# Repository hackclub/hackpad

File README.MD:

Talk to @Ace (Zohair shaik) on slack Gmail: Zohairshaik7@gmail.com Discord: autohackingcodes2079Hi this is my hackpad submission:

________________________________________________
Why I made it:

Was pretty bored and saw some macropads on insta so i got inspired..
________________________________________________
What I need:

7x Cherry MX switches
2x SK6812 MINI Leds
7x Blank DSA Keycaps
________________________________________________

______________________________________________
Firmware used:

KMK

_______________________________________________

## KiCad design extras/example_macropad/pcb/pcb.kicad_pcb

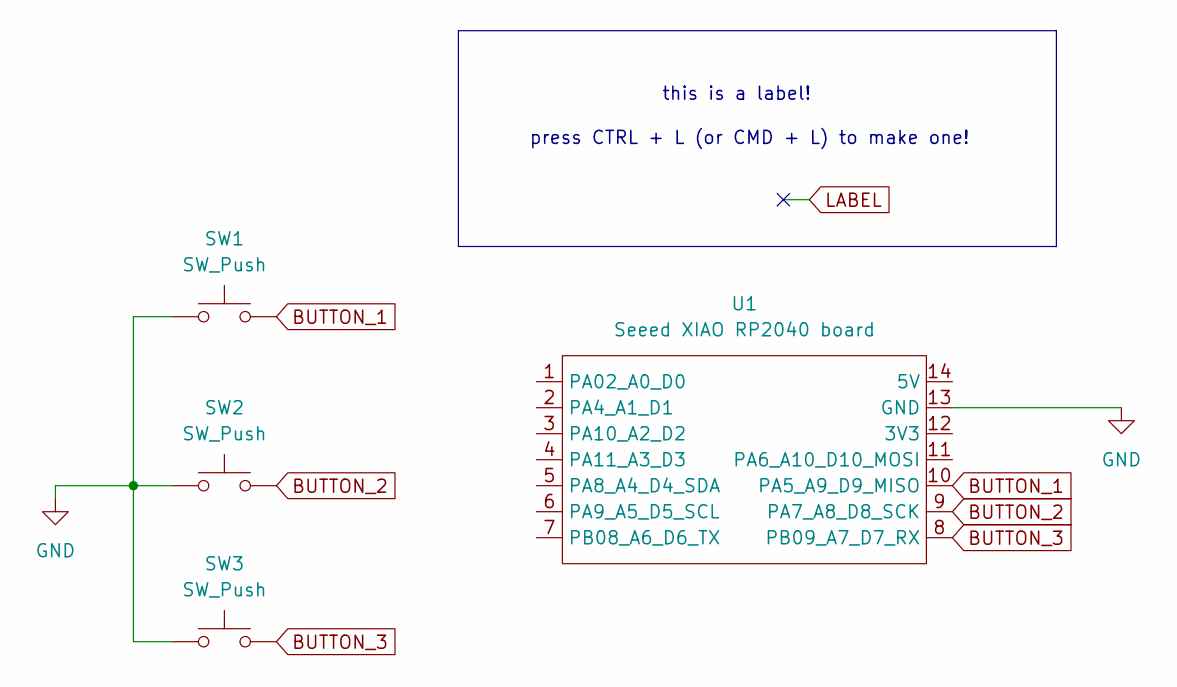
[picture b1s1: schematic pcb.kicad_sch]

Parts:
SW1, SW2, SW3: SW_Push; SW_Cherry_MX_1.00u_PCB
U1: Seeed XIAO RP2040 board; XIAO-Generic-Hybrid-14P-2.54-21X17.8MM

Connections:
BUTTON_1: SW1.2, U1.10 (PA5_A9_D9_MISO)
BUTTON_2: SW2.2, U1.9 (PA7_A8_D8_SCK)
BUTTON_3: SW3.2, U1.8 (PB09_A7_D7_RX)
GND: SW1.1, SW2.1, SW3.1, U1.13 (GND)

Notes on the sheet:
press CTRL + L (or CMD + L) to make one!
this is a label!

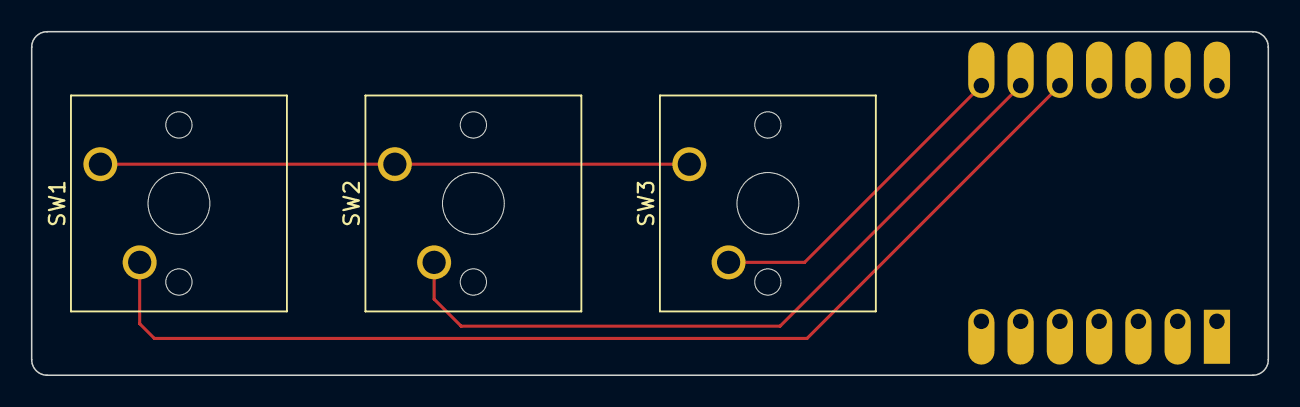
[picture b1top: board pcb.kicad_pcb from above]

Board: 2 copper layers, 80.0 x 22.2 mm, 4 parts (1 on the bottom side), 4 nets.

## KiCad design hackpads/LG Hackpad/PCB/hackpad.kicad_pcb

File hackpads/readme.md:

# madpad

* Keyboard Maintainer: [Meghana Madiraju](https://github.com/MeghanaM4)
* Hardware Supported: *The PCBs, controllers supported*
* Hardware Availability: *Links to where you can find this hardware*

Make example for this keyboard (after setting up your build environment):

    make madpad:default

Flashing example for this keyboard:

    make madpad:default:flash

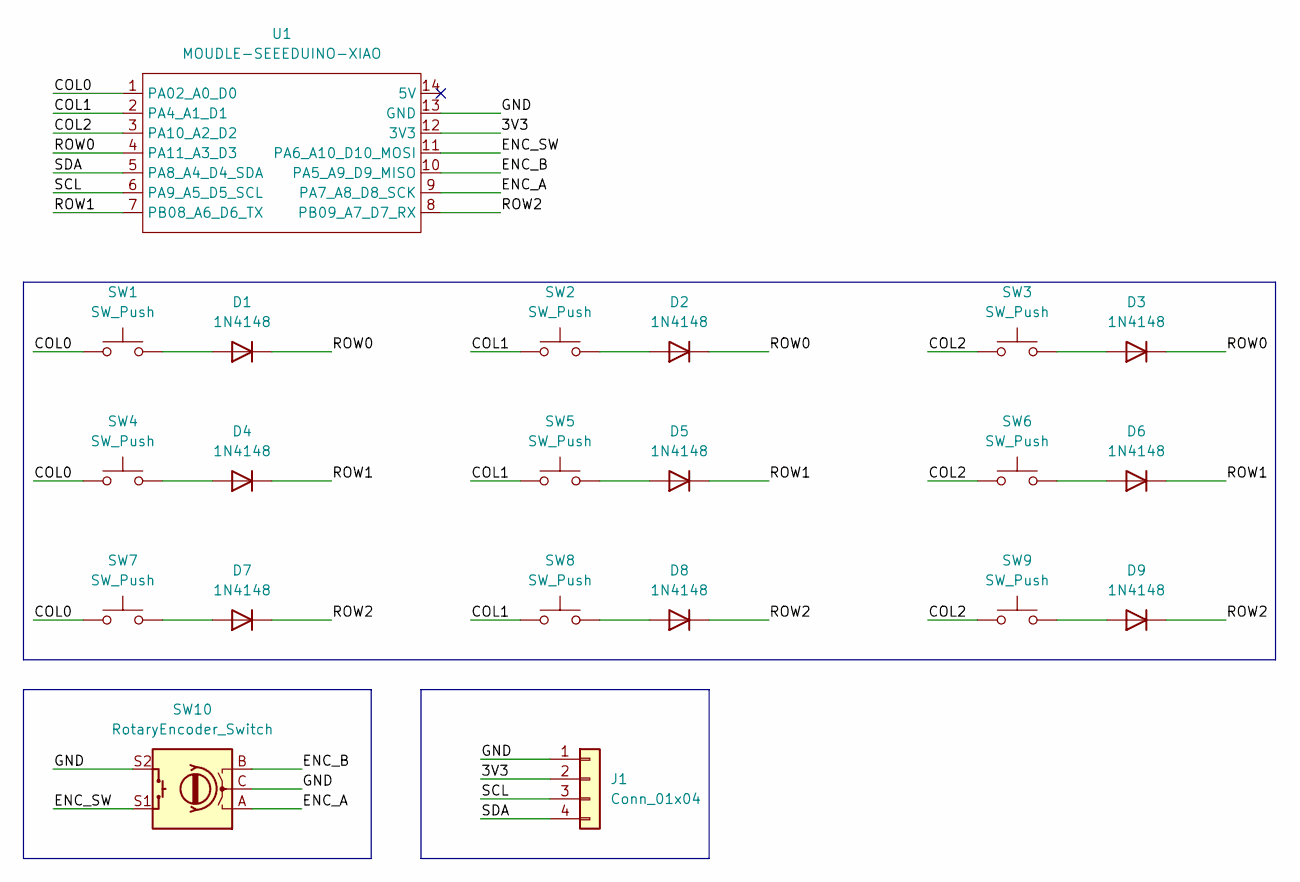
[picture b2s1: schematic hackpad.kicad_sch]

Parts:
D1, D2, D3, D4, D5, D6, D7, D8, D9: 1N4148; D_DO-35_SOD27_P7.62mm_Horizontal
J1: Conn_01x04; PinHeader_1x04_P2.54mm_Vertical
SW1, SW2, SW3, SW4, SW5, SW6, SW7, SW8, SW9: SW_Push; SW_Cherry_MX_1.00u_PCB
SW10: RotaryEncoder_Switch; RotaryEncoder_Alps_EC11E-Switch_Vertical_H20mm
U1: MOUDLE-SEEEDUINO-XIAO; XIAO-Generic-Hybrid-14P-2.54-21X17.8MM

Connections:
/3V3: J1.2, U1.12 (3V3)
/COL0: SW1.1, SW4.1, SW7.1, U1.1 (PA02_A0_D0)
/COL1: SW2.1, SW5.1, SW8.1, U1.2 (PA4_A1_D1)
/COL2: SW3.1, SW6.1, SW9.1, U1.3 (PA10_A2_D2)
/ENC_A: SW10.A, U1.9 (PA7_A8_D8_SCK)
/ENC_B: SW10.B, U1.10 (PA5_A9_D9_MISO)
/ENC_SW: SW10.S1, U1.11 (PA6_A10_D10_MOSI)
/GND: J1.1, SW10.C, SW10.S2, U1.13 (GND)
/ROW0: D1.1 (K), D2.1 (K), D3.1 (K), U1.4 (PA11_A3_D3)
/ROW1: D4.1 (K), D5.1 (K), D6.1 (K), U1.7 (PB08_A6_D6_TX)
/ROW2: D7.1 (K), D8.1 (K), D9.1 (K), U1.8 (PB09_A7_D7_RX)
/SCL: J1.3, U1.6 (PA9_A5_D5_SCL)
/SDA: J1.4, U1.5 (PA8_A4_D4_SDA)
unnamed: D1.2 (A), SW1.2
unnamed: D2.2 (A), SW2.2
unnamed: D3.2 (A), SW3.2
unnamed: D4.2 (A), SW4.2
unnamed: D5.2 (A), SW5.2
unnamed: D6.2 (A), SW6.2
unnamed: D7.2 (A), SW7.2
unnamed: D8.2 (A), SW8.2
unnamed: D9.2 (A), SW9.2

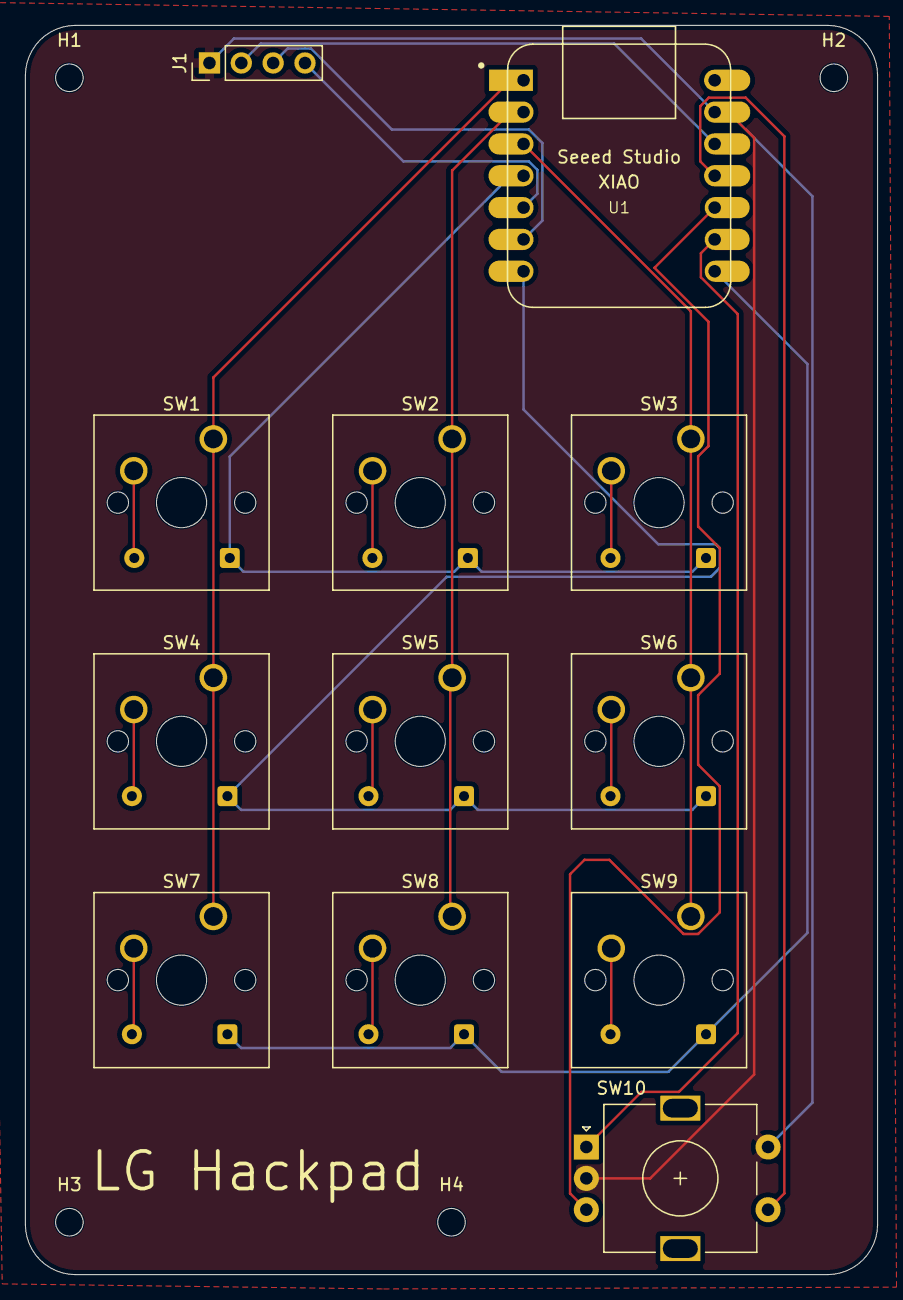
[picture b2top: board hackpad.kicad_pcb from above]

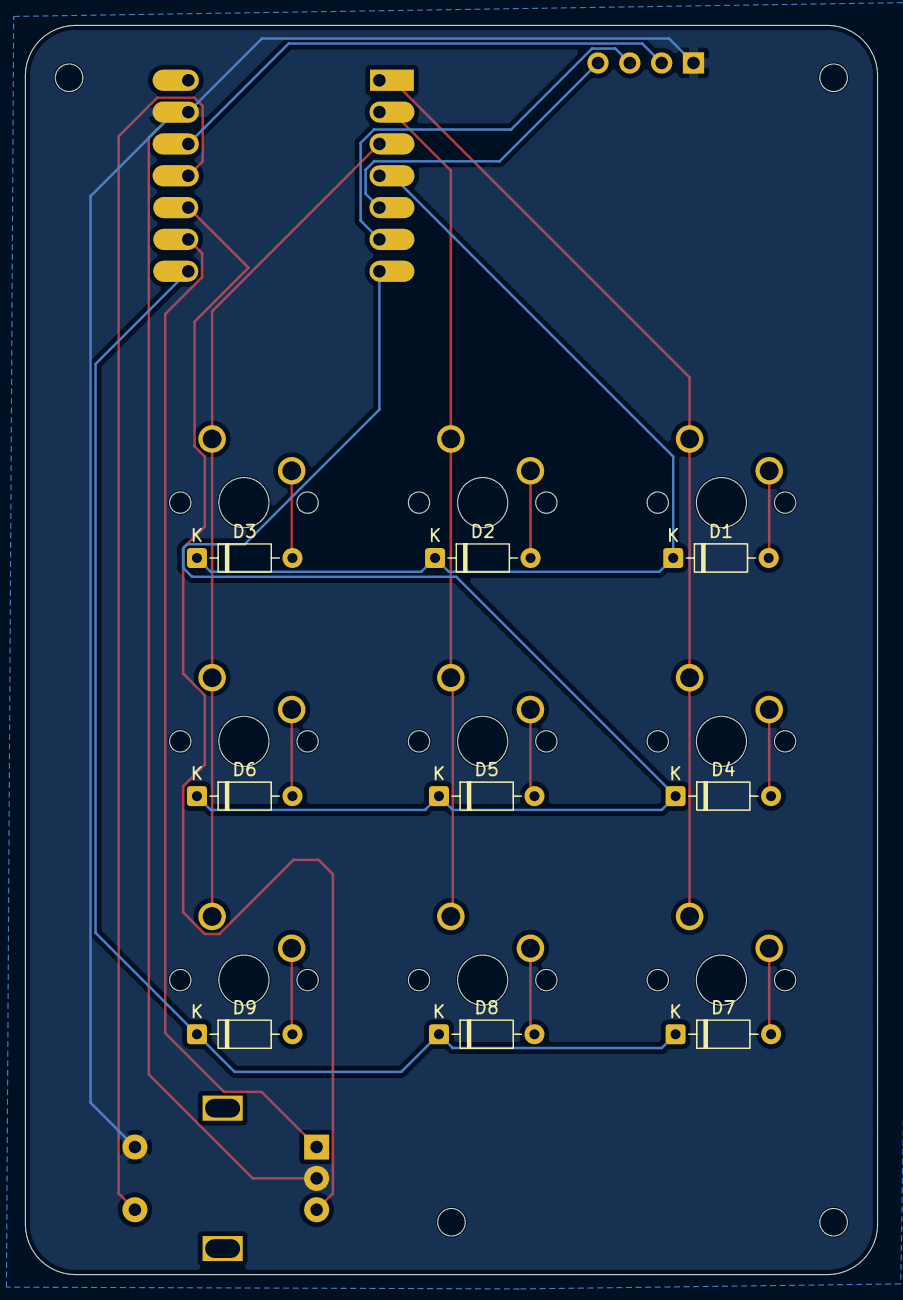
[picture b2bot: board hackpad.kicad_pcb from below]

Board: 2 copper layers, 68.0 x 99.7 mm, 25 parts (9 on the bottom side), 22 nets.

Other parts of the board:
H1, H2, H3, H4: MountingHole_2.2mm_M2

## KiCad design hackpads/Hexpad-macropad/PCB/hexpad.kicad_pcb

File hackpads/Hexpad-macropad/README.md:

# Hexpad — a hex-shaped 6-key macropad

A 6-key (3×2) macropad with a rotary encoder: 3D-printed case, custom 2-layer PCB,
and KMK firmware, driven by a **Seeed XIAO RP2040**. Keys wire **direct to GPIO**
(no matrix, no diodes), and the encoder handles volume/scroll.

## Inspiration & challenges

I wanted a compact editing/clipboard pad with a volume knob that didn't look like
every other square macropad — so Hexpad uses a hexagonal silhouette around a
centered 3×2 key cluster with the encoder up top.

Two things were genuinely fiddly. First, the original top-plate CAD came out of an
early IDE session malformed — the plate solid was fused to a stray slab 74 mm
below it, so it "levitated" in the slicer. I had to reverse-engineer the real
dimensions from the STEP geometry and rebuild the plate as a clean parametric
build123d script. Second, rather than hand-draw the board I generated the PCB
programmatically with KiCad's `pcbnew` API from a single coordinate spec, which
guarantees the switch, encoder, and mounting-hole positions line up exactly with
the printed plate (19.05 mm pitch, mounts at ±31 mm).

## Gallery

| Schematic | PCB | Case |
|-----------|-----|------|
|  |  |  |

## Bill of materials

| Qty | Part | Notes |
|-----|------|-------|
| 1 | Seeed XIAO RP2040 | MCU, mounted on the back; USB-C exits the front edge |
| 6 | Cherry MX (or compatible) switch | direct-wired, one GPIO each |
| 1 | Alps EC11 rotary encoder w/ switch | A/B + push → 3 GPIO, common → GND |
| 4 | M2 screw (~6 mm) | through the case into the plate's corner posts |
| 6 / 1 | MX keycaps / encoder knob | cosmetic |
| 0 | diodes | **none** — direct wiring is valid for ≤7 keys |

## Pin map

| Input | XIAO pin | | Input | XIAO pin |
|-------|----------|-|-------|----------|
| SW1–SW3 (front) | D0, D1, D2 | | Encoder A / B | D8 / D9 |
| SW4–SW6 (rear) | D3, D6, D7 | | Encoder push | D10 |

`D4`/`D5` (SDA/SCL) are left free for a future OLED. All inputs use the RP2040's
internal pull-ups (a press/turn pulls the pin to GND).

## Folder contents

| Folder | Files |
|--------|-------|
| `CAD/` | `hexpad_assembly.step` — full case (top plate + bottom case), name engraved on the plate |
| `PCB/` | `hexpad.kicad_pro` / `.kicad_sch` / `.kicad_pcb` / `.kicad_sym` / `sym-lib-table`, plus `hexpad-gerbers.zip` (JLCPCB-ready) |
| `Firmware/` | `code.py` (KMK keymap) + flashing/remapping `README.md` |
| `docs/images/` | render, schematic, PCB, and case images |

- **PCB:** 2-layer, **76 × 74 mm**, silkscreen-branded "Hexpad". DRC: 0 errors,
  0 unconnected (silkscreen / courtyard warnings only). Schematic ERC: 0 violations.
- **Firmware:** KMK (CircuitPython). Default keymap: front row Copy/Paste/Cut,
  rear row Undo/Redo/Save, encoder = volume (press = mute).
- **Case:** 3D-printed; "Hexpad" engraved into the top plate's front margin.

## Toolchain

build123d (CAD → STEP) · KiCad 10 (PCB) · Bambu Studio (slicing) · CircuitPython + KMK.

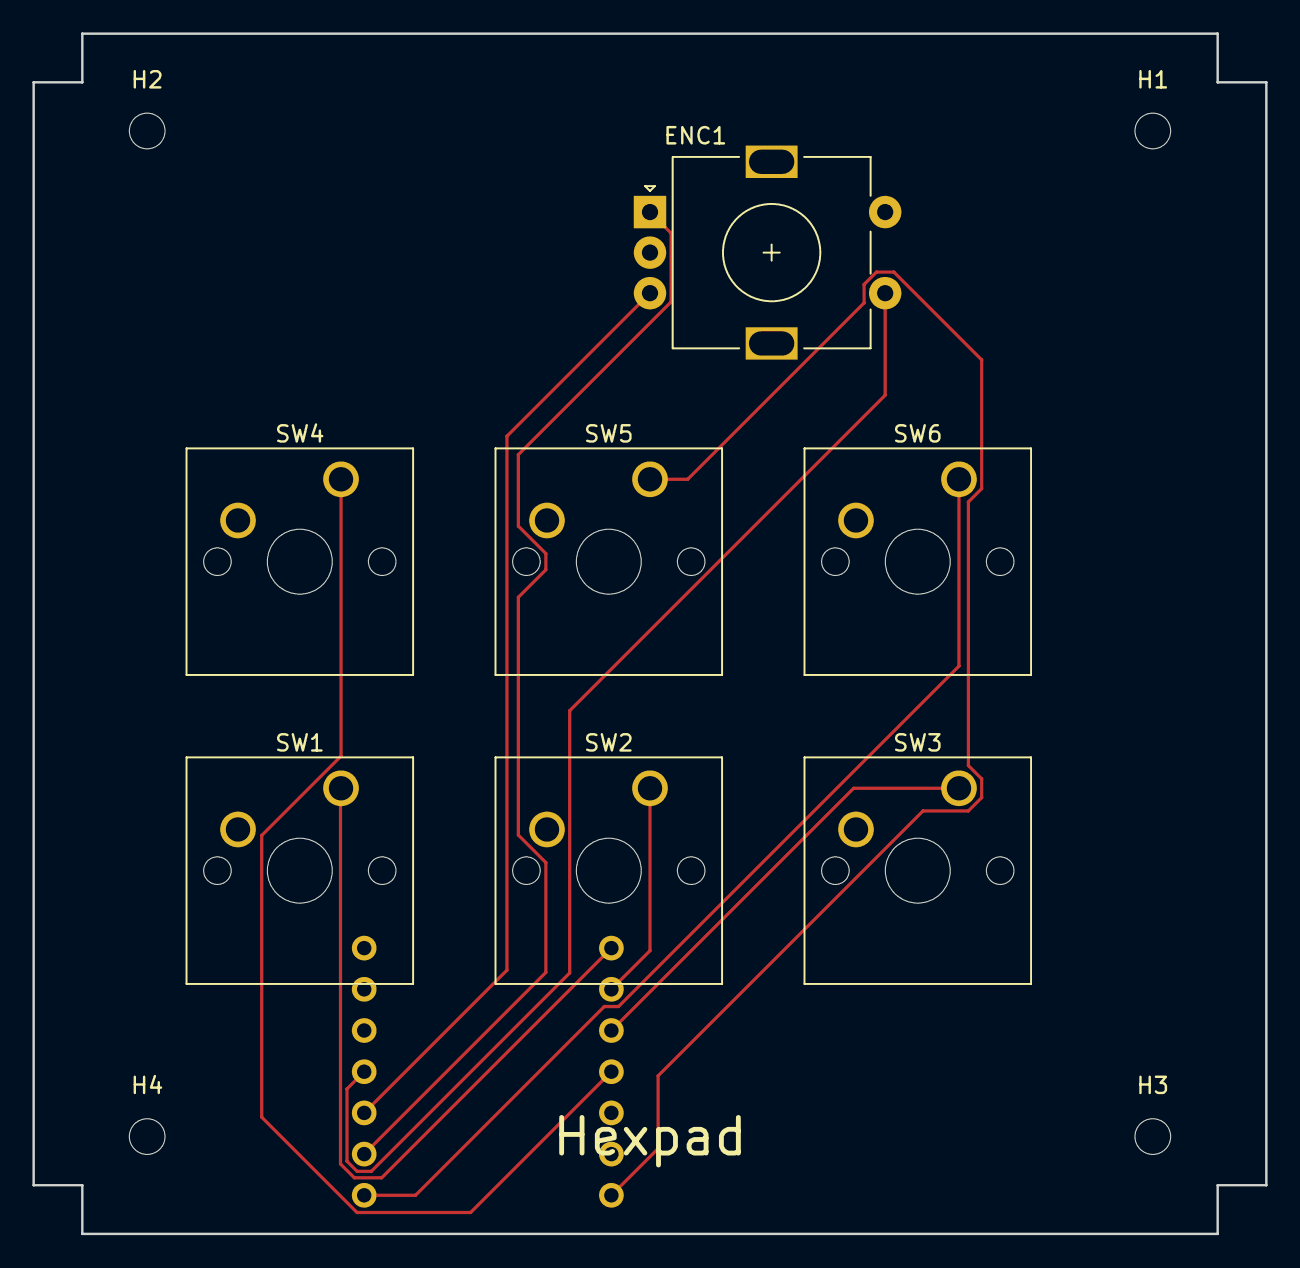
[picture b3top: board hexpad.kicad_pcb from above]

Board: 2 copper layers, 76.0 x 74.0 mm, 12 parts (1 on the bottom side), 10 nets.

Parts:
ENC1: EC11; RotaryEncoder_Alps_EC11E-Switch_Vertical_H20mm
H1, H2, H3, H4: M2; MountingHole_2.2mm_M2
SW1, SW2, SW3, SW4, SW5, SW6: SW_MX; SW_Cherry_MX_1.00u_PCB
U1: XIAO-RP2040

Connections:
ENCA: ENC1.A, U1.9
ENCB: ENC1.B, U1.10
ENCSW: ENC1.S1, U1.11
GND: ENC1.C, ENC1.MP, ENC1.S2, SW1.2, SW2.2, SW3.2, SW4.2, SW5.2, SW6.2, U1.13
SW1: SW1.1, U1.1
SW2: SW2.1, U1.2
SW3: SW3.1, U1.3
SW4: SW4.1, U1.4
SW5: SW5.1, U1.7
SW6: SW6.1, U1.8

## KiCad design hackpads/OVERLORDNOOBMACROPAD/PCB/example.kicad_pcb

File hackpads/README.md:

Github README

# Stoopid_Pad

<b>Running from the 10th to the 25th of November, You ship AI software, We ship AI hardware.</b>

<br>

## BOM:

-  Seeed XIAO RP2040

- 8x Blank DSA keycaps

- 8x Cherry MX switches

- 1x EC11 Encoder

- 1x PCB - black

- M3x16mm screws

- 3D printed parts
-  4x 4.7kΩ. resistors
- 1x SSD1306 OLED Display

## Stoopid_Pad:

I had a lot of fun making the macropad, this was my first time making a PCB, though I found it more difficult to finish off the case because I have zero experience CADding and my potato laptop did not enjoy my attempts to import the pcb with keys and everything into OnShape. I was dreading the PCB part but it was surprisingly fun :D

## Images!

Finished Macropad:

Schematic:

PCB!:

Another Macropad photo because why not:

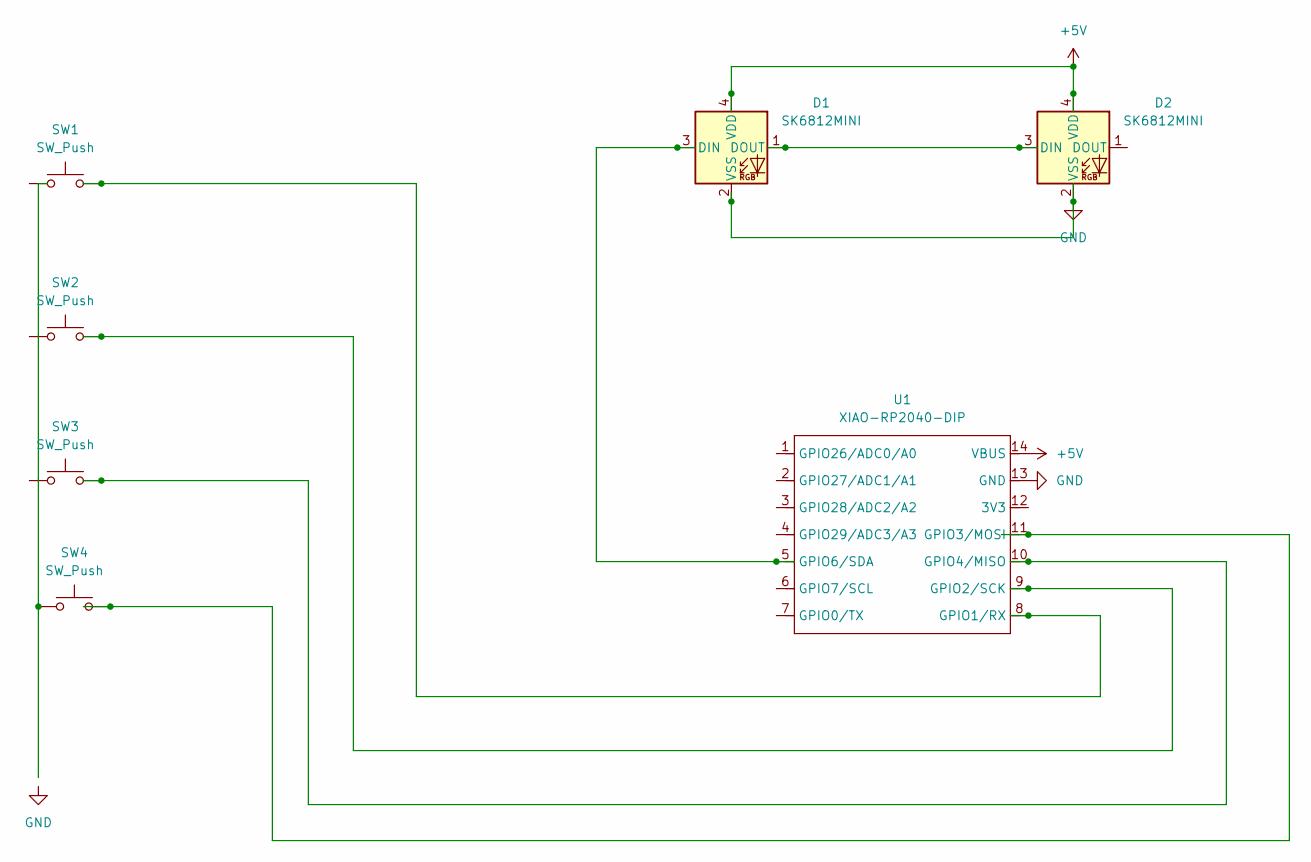
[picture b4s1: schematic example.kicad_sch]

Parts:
D1, D2: SK6812MINI; LED_SK6812MINI_PLCC4_3.5x3.5mm_P1.75mm
SW1, SW2, SW3, SW4: SW_Push; SW_Cherry_MX_1.00u_PCB
U1: XIAO-RP2040-DIP; XIAO-RP2040-SMD

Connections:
+5V: D1.4 (VDD), D2.4 (VDD), U1.14 (VBUS)
GND: D1.2 (VSS), D2.2 (VSS), U1.13 (GND)
unnamed: D1.3 (DIN), U1.5 (GPIO6/SDA)
unnamed: D1.1 (DOUT), D2.3 (DIN)
unnamed: SW1.2, U1.8 (GPIO1/RX)
unnamed: SW2.2, U1.9 (GPIO2/SCK)
unnamed: SW4.2, U1.11 (GPIO3/MOSI)
unnamed: SW3.2, U1.10 (GPIO4/MISO)

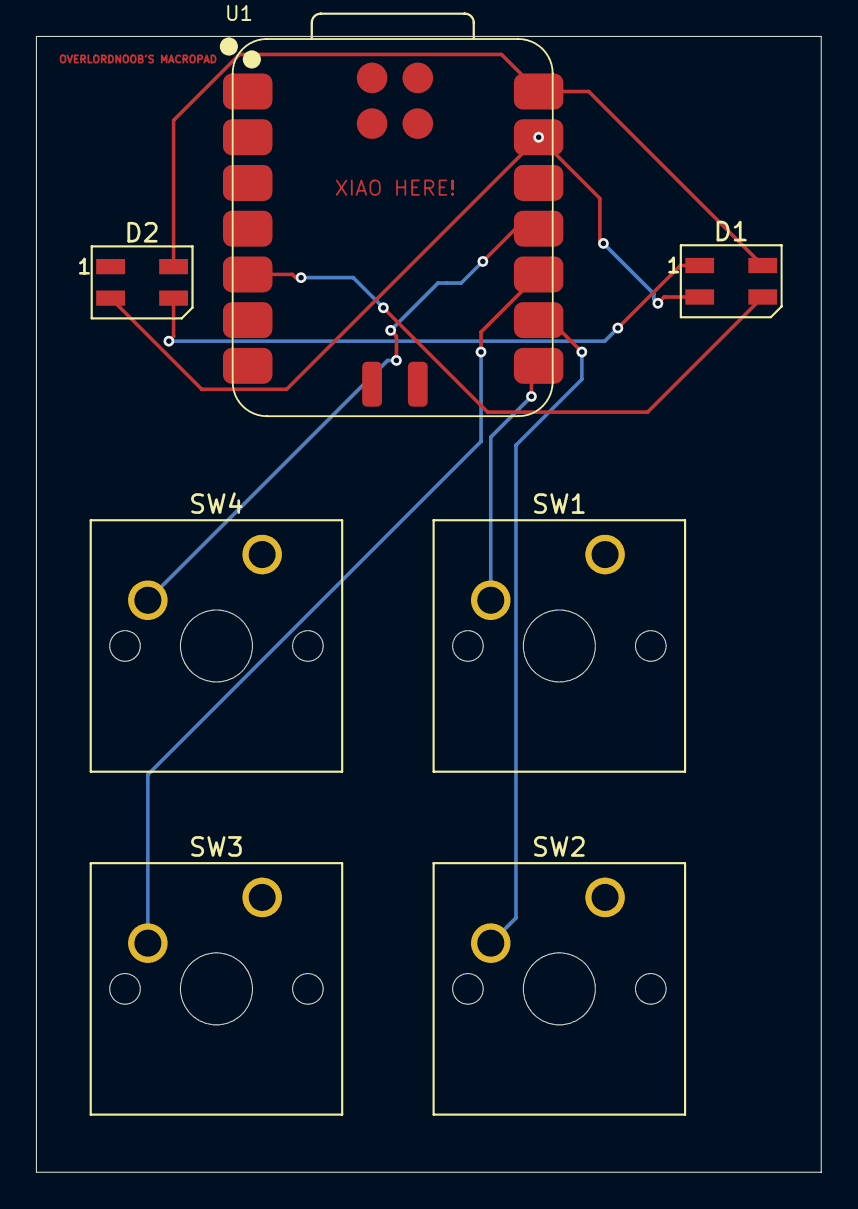
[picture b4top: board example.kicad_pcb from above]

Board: 2 copper layers, 43.6 x 63.1 mm, 7 parts (0 on the bottom side), 8 nets.

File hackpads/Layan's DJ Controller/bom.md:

# Hackpad - Bill of Materials

- 1x XIAO SEEED RP2040: XIAO-RP2040-DIP
- 1x MCP23017-SO: Package_SO:SOIC-28W_7.5x17.9mm_P1.27mm
- 2x LEDs: LED_SK6812MINI_PLCC4_3.5x3.5mm_P1.75mm
- 2x Bourns slide potentiometer: TRIM_PTA4543-2015DPA103
- 2x 4.7kΩ resistors: R_Axial_DIN0204_L3.6mm_D1.6mm_P7.62mm_Horizontal
- 8x Cherry MX switches: SW_Cherry_MX_1.00u_PCB
- 2x Alps rotary encoders: RotaryEncoder_Alps_EC11E_Vertical_H20mm

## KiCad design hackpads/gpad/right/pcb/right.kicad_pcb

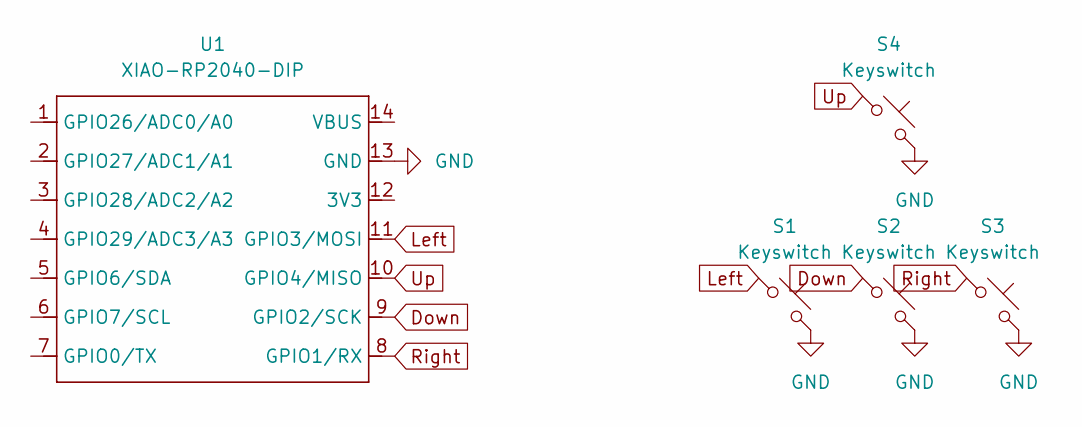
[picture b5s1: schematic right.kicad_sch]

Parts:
S1, S2, S3, S4: Keyswitch; MX_PCB_1.00u
U1: XIAO-RP2040-DIP; Seeed_XIAO_RP2040

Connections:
Down: S2.1, U1.9 (GPIO2/SCK)
GND: S1.2, S2.2, S3.2, S4.2, U1.13 (GND)
Left: S1.1, U1.11 (GPIO3/MOSI)
Right: S3.1, U1.8 (GPIO1/RX)
Up: S4.1, U1.10 (GPIO4/MISO)

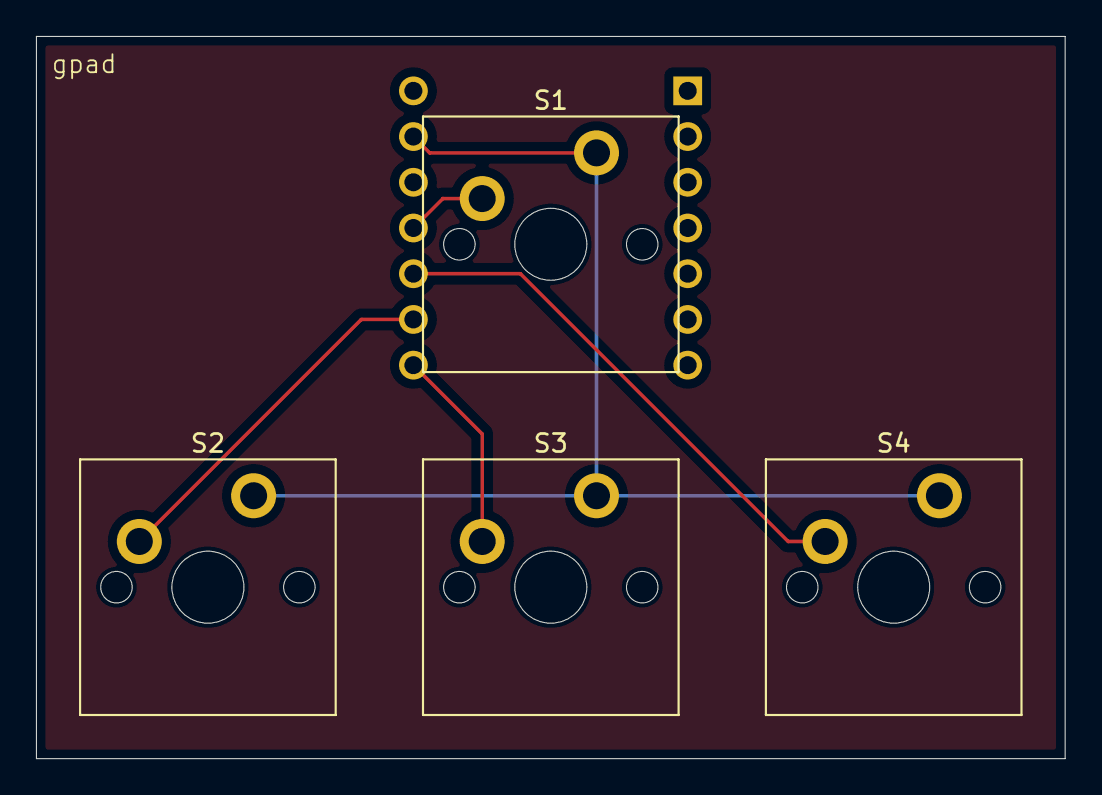
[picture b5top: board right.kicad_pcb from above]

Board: 2 copper layers, 57.2 x 40.1 mm, 5 parts (1 on the bottom side), 5 nets.

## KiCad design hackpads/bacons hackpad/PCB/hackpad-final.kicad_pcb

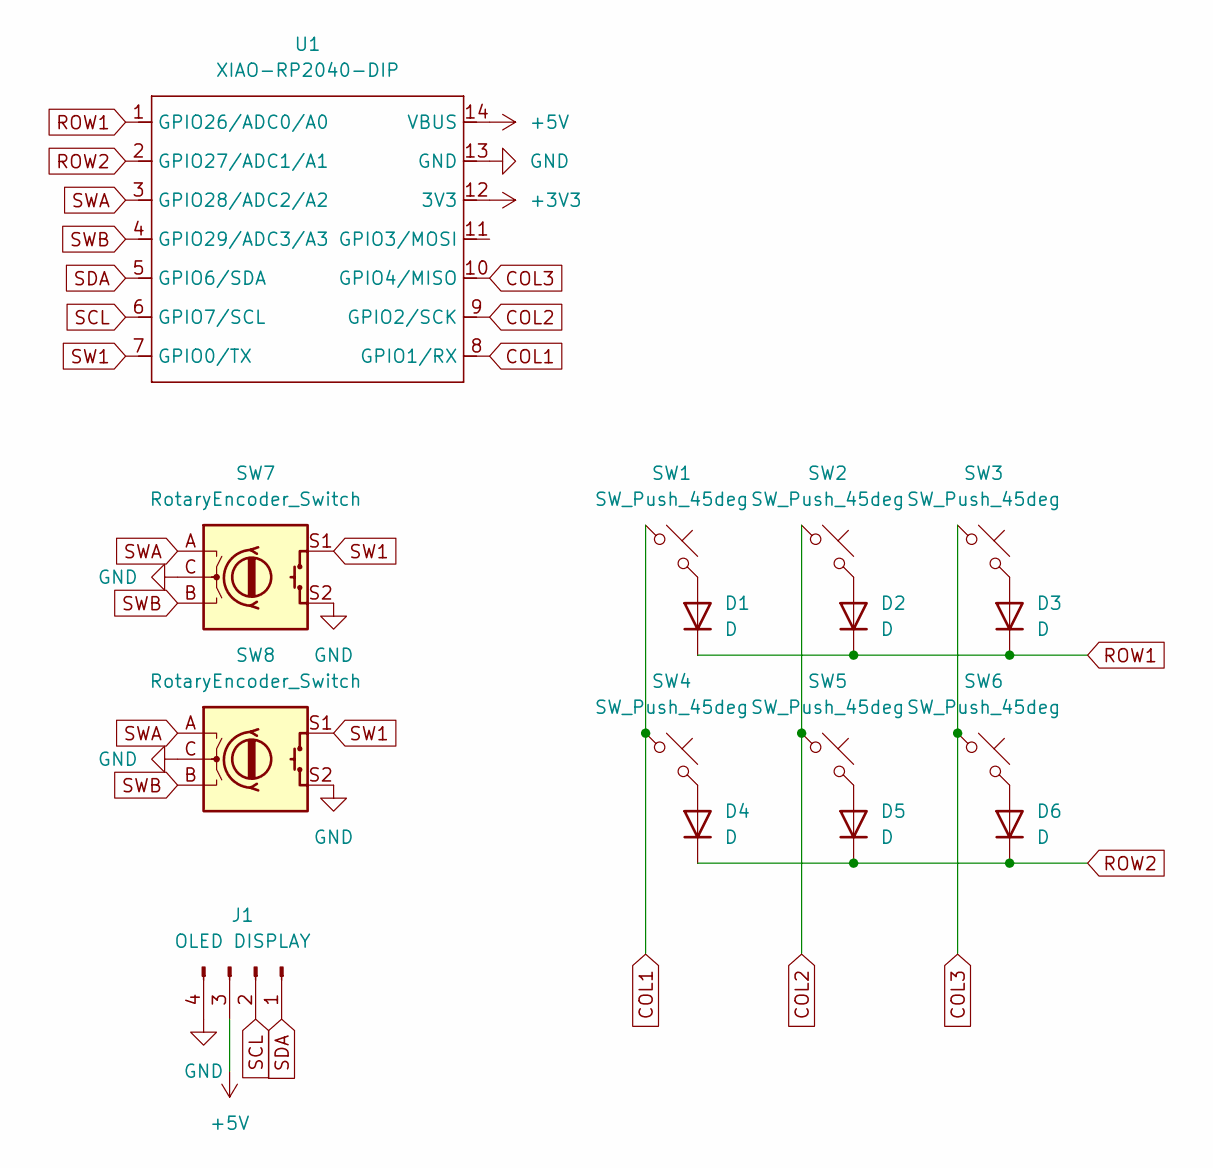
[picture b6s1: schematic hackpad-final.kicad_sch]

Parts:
D1, D2, D3, D4, D5, D6: D; D_DO-35_SOD27_P7.62mm_Horizontal
J1: OLED DISPLAY; SSD1306-0.91-OLED-4pin-128x32
SW1, SW2, SW3, SW4, SW5, SW6: SW_Push_45deg; SW_Cherry_MX_1.00u_PCB
SW7, SW8: RotaryEncoder_Switch; RotaryEncoder_Alps_EC11E-Switch_Vertical_H20mm
U1: XIAO-RP2040-DIP; XIAO-Generic-Hybrid-14P-2.54-21X17.8MM

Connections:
+3V3: U1.12 (3V3)
+5V: J1.3, U1.14 (VBUS)
COL1: SW1.1, SW4.1, U1.8 (GPIO1/RX)
COL2: SW2.1, SW5.1, U1.9 (GPIO2/SCK)
COL3: SW3.1, SW6.1, U1.10 (GPIO4/MISO)
GND: J1.4, SW7.C, SW7.S2, SW8.C, SW8.S2, U1.13 (GND)
unnamed: D1.2 (A), SW1.2
unnamed: D2.2 (A), SW2.2
unnamed: D3.2 (A), SW3.2
unnamed: D4.2 (A), SW4.2
unnamed: D5.2 (A), SW5.2
unnamed: D6.2 (A), SW6.2
ROW1: D1.1 (K), D2.1 (K), D3.1 (K), U1.1 (GPIO26/ADC0/A0)
ROW2: D4.1 (K), D5.1 (K), D6.1 (K), U1.2 (GPIO27/ADC1/A1)
SCL: J1.2, U1.6 (GPIO7/SCL)
SDA: J1.1, U1.5 (GPIO6/SDA)
SW1: SW7.S1, SW8.S1, U1.7 (GPIO0/TX)
SWA: SW7.A, SW8.A, U1.3 (GPIO28/ADC2/A2)
SWB: SW7.B, SW8.B, U1.4 (GPIO29/ADC3/A3)

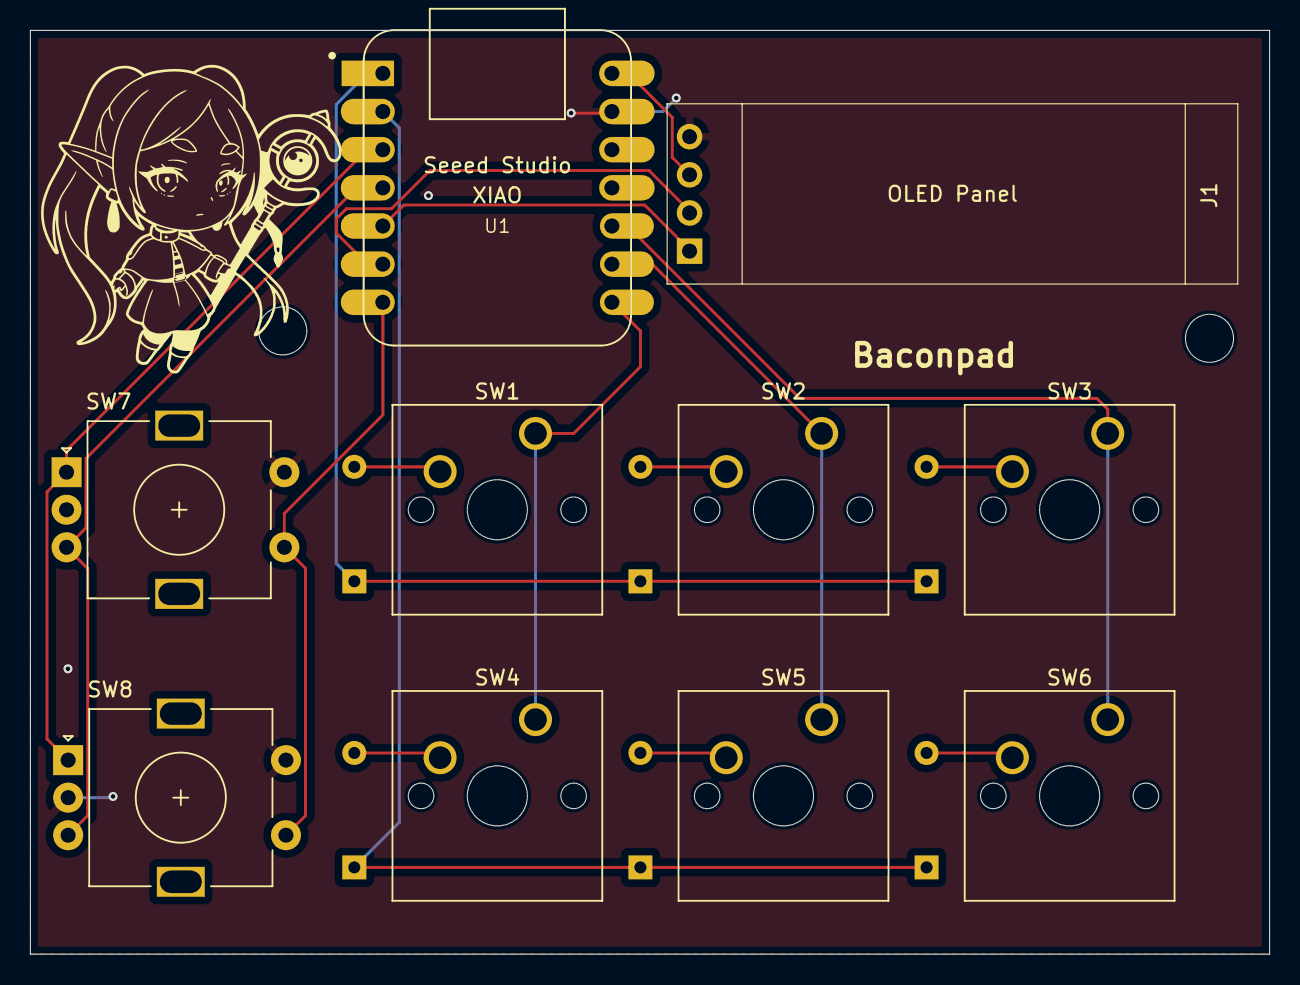
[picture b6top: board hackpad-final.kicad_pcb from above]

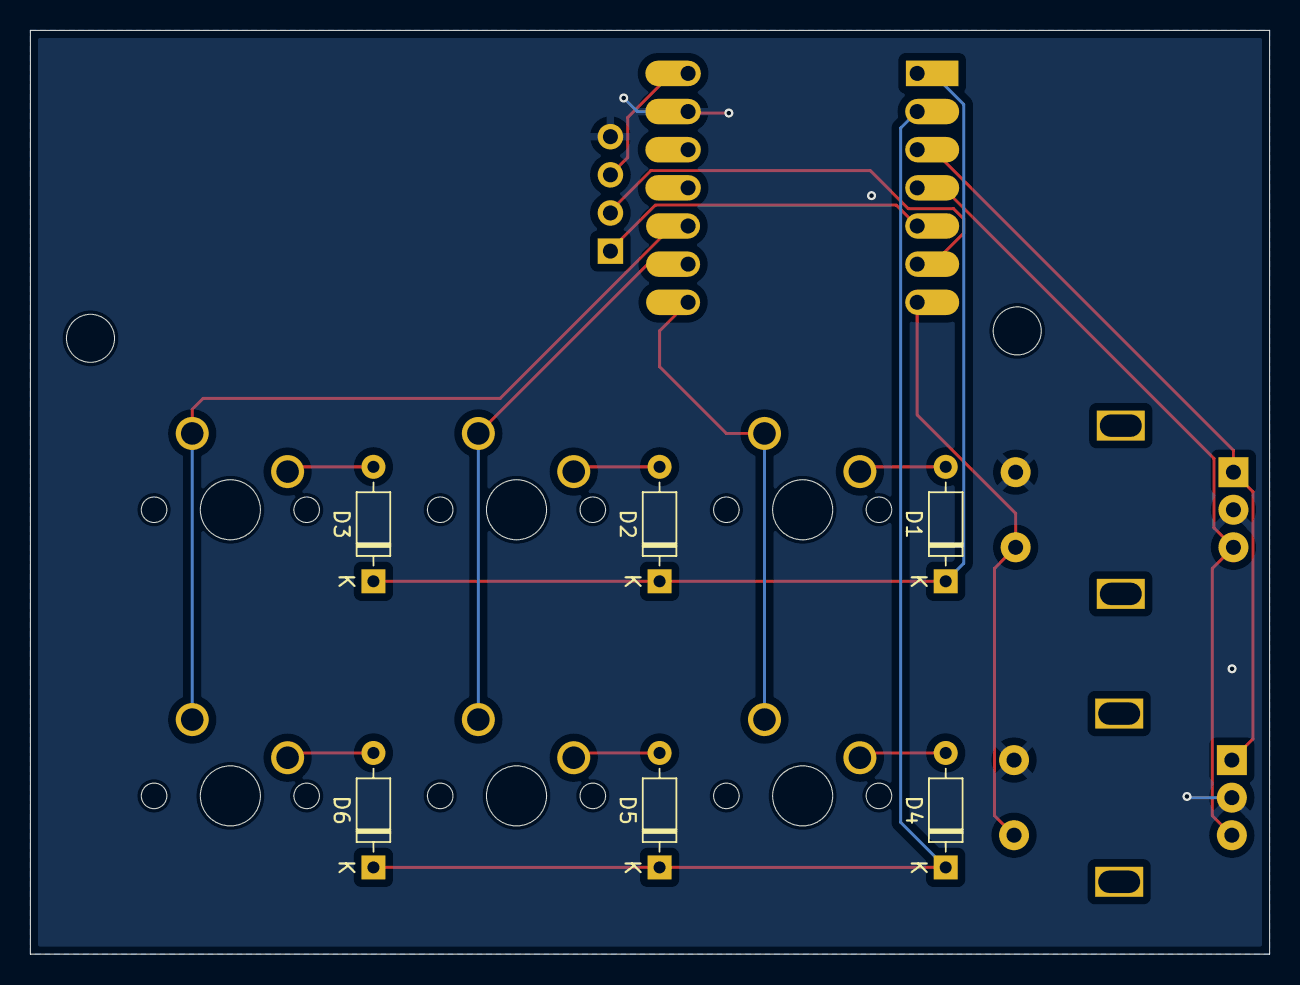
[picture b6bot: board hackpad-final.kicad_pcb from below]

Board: 2 copper layers, 82.5 x 61.5 mm, 16 parts (6 on the bottom side), 18 nets.

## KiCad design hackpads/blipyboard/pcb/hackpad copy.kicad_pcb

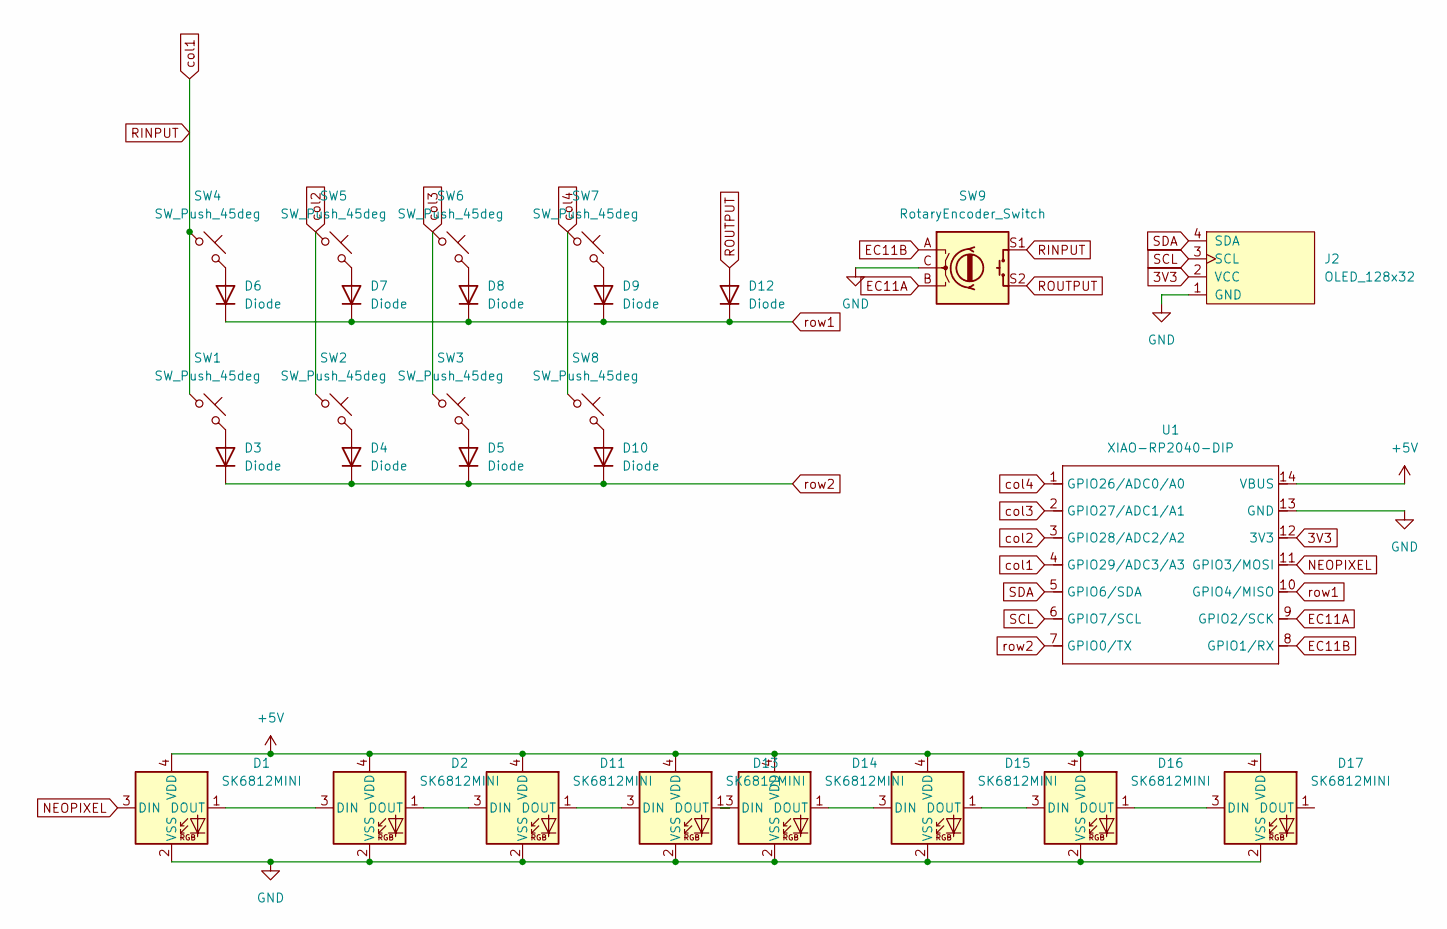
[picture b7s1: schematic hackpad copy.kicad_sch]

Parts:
D1, D2, D11, D13, D14, D15, D16, D17: SK6812MINI; LED_SK6812MINI_PLCC4_3.5x3.5mm_P1.75mm
D3, D4, D5, D6, D7, D8, D9, D10, D12: Diode; D_DO-35_SOD27_P7.62mm_Horizontal
J2: OLED_128x32
SW1, SW2, SW3, SW4, SW5, SW6, SW7, SW8: SW_Push_45deg; SW_Cherry_MX_1.00u_PCB
SW9: RotaryEncoder_Switch; RotaryEncoder_Alps_EC11E-Switch_Vertical_H20mm
U1: XIAO-RP2040-DIP

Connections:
3V3: J2.2 (VCC), U1.12 (3V3)
+5V: D1.4 (VDD), D2.4 (VDD), D11.4 (VDD), D13.4 (VDD), D14.4 (VDD), D15.4 (VDD), D16.4 (VDD), D17.4 (VDD), U1.14 (VBUS)
EC11A: SW9.B, U1.9 (GPIO2/SCK)
EC11B: SW9.A, U1.8 (GPIO1/RX)
GND: D1.2 (VSS), D2.2 (VSS), D11.2 (VSS), D13.2 (VSS), D14.2 (VSS), D15.2 (VSS), D16.2 (VSS), D17.2 (VSS), J2.1 (GND), SW9.C, U1.13 (GND)
NEOPIXEL: D1.3 (DIN), U1.11 (GPIO3/MOSI)
unnamed: D1.1 (DOUT), D2.3 (DIN)
unnamed: D3.2 (A), SW1.2
unnamed: D4.2 (A), SW2.2
unnamed: D5.2 (A), SW3.2
unnamed: D6.2 (A), SW4.2
unnamed: D7.2 (A), SW5.2
unnamed: D8.2 (A), SW6.2
unnamed: D9.2 (A), SW7.2
unnamed: D10.2 (A), SW8.2
unnamed: D2.1 (DOUT), D11.3 (DIN)
unnamed: D11.1 (DOUT), D13.3 (DIN)
unnamed: D13.1 (DOUT), D14.3 (DIN)
unnamed: D14.1 (DOUT), D15.3 (DIN)
unnamed: D15.1 (DOUT), D16.3 (DIN)
unnamed: D16.1 (DOUT), D17.3 (DIN)
RINPUT: SW1.1, SW4.1, SW9.S1, U1.4 (GPIO29/ADC3/A3)
ROUTPUT: D12.2 (A), SW9.S2
SCL: J2.3 (SCL), U1.6 (GPIO7/SCL)
SDA: J2.4 (SDA), U1.5 (GPIO6/SDA)
col2: SW2.1, SW5.1, U1.3 (GPIO28/ADC2/A2)
col3: SW3.1, SW6.1, U1.2 (GPIO27/ADC1/A1)
col4: SW7.1, SW8.1, U1.1 (GPIO26/ADC0/A0)
row1: D6.1 (K), D7.1 (K), D8.1 (K), D9.1 (K), D12.1 (K), U1.10 (GPIO4/MISO)
row2: D3.1 (K), D4.1 (K), D5.1 (K), D10.1 (K), U1.7 (GPIO0/TX)

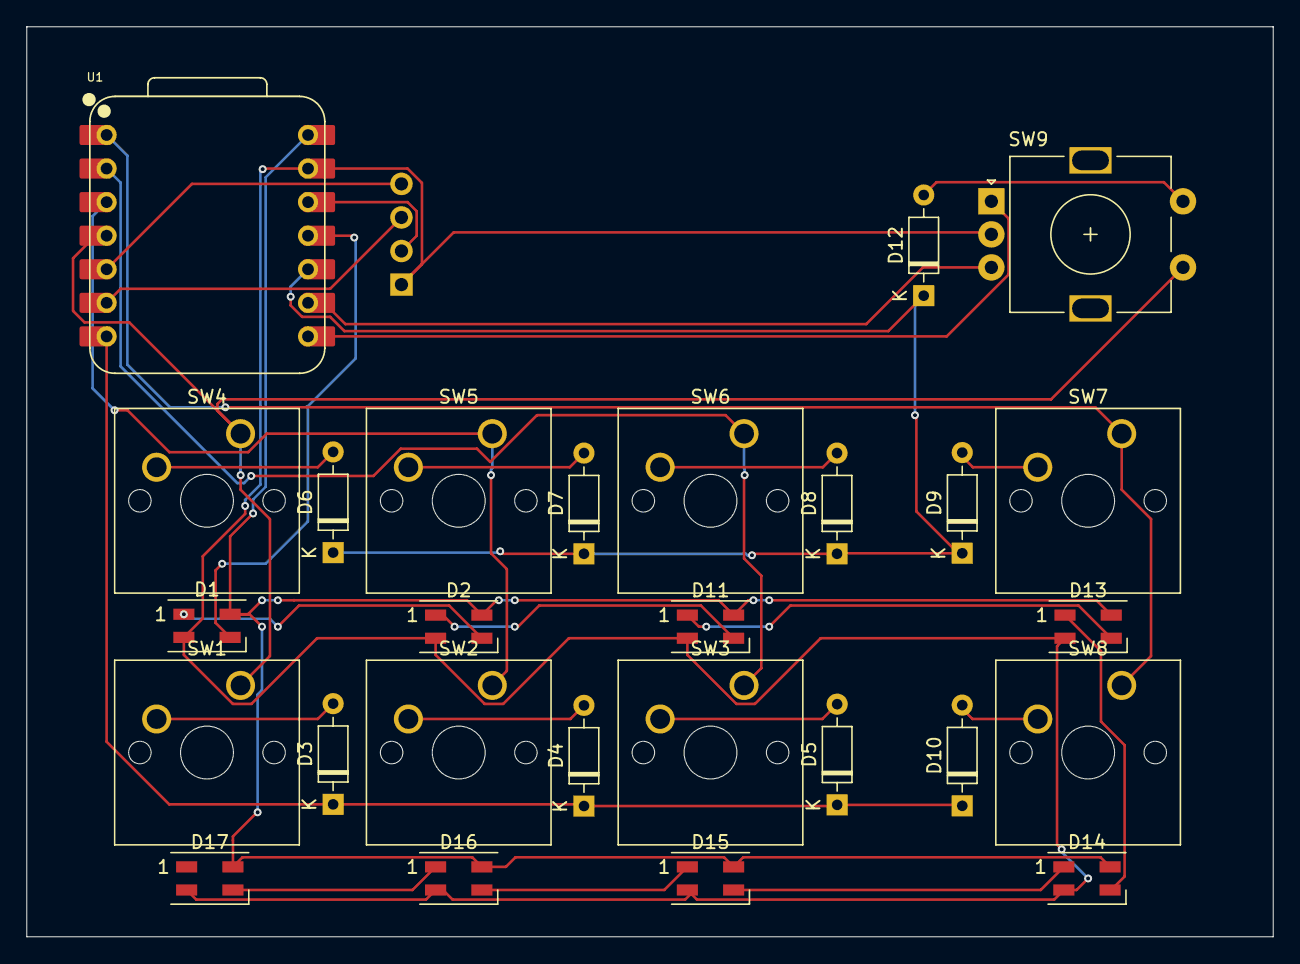
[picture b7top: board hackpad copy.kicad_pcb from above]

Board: 2 copper layers, 94.3 x 68.9 mm, 28 parts (0 on the bottom side), 30 nets.
